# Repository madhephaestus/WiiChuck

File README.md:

# WiiChuck
An Arduino library for talking to every extension controller made for the Wii including the Nunchuk and Classic Controller over I²C.

## Supported Controllers:

* Nunchuk
* Classic Controller
* Guitar Hero Guitar
* Guitar Hero Drums
* DJ Hero
* Drawesome Tablet
* Taiko Drums

# Mapping

All controllers have been mapped across a single readable array so that code written for one Wii accessort can be made generic for all of Wii accessory devices. The values that come from the controller are scaled to a 0-255 range for all analog and for all digital values. Each value is stored in a single byte in the 'values[]' array, a public member of the accessory class.

Initialize the controller first:

```
nunchuck1.begin();
```

In loop, when reading the controller values, first call:

```
nunchuck1.readData();    // Read inputs and update maps
```

Then read the controller values out of the 'values[]' array:

```
uint8_t joystickValueX = nunchuck1.values[1];
uint8_t joystickValueY = nunchuck1.values[2];

...

uint8_t lastValue = nunchuck1.values[19];

```

## Nunchuck mapping

```
values[0]=map(getJoyX(),0,255,0,255);
values[1]=map(getJoyY(),0,255,0,255);
values[2]=map(getRollAngle(),0,1024,0,256);
values[3]=map(getPitchAngle(),0,1024,0,256);
values[4]=map(getAccelX(),0,1024,0,256);
values[5]=map(getAccelY(),0,1024,0,256);

values[6]=map(getAccelZ(),0,1024,0,256);
values[7]=0;
values[8]=0;
values[9]=0;
values[10]=getButtonZ()?255:0;
values[11]=getButtonC()?255:0;
values[12]=0;
values[13]=0;

values[14]=0;
values[15]=0;
values[16]=0;

values[17]=0;
values[18]=0;
```

## Classic Controller Mapping

```
values[0]=map(getJoyXLeft(),0,64,0,256);
values[1]=map(getJoyYLeft(),0,64,0,256);
values[2]=map(getJoyXRight(),0,32,0,256);
values[3]=map(getJoyYRight(),0,32,0,256);
values[4]=0;
values[5]=0;

values[6]=getPadRight()?255:(getPadLeft()?0:128);
values[7]=getPadDown()?0:(getPadUp()?255:128);
values[8]=getButtonX()?255:0;
values[9]=getButtonY()?255:0;
values[10]=getButtonZLeft()?255:0;
values[11]=map(getTriggerLeft(),0,32,0,256);
values[12]=getButtonA()?255:0;
values[13]=getButtonB()?255:0;

values[14]=getButtonMinus()?0:(getButtonPlus()?255:128);
values[15]=getButtonHome()?255:0;
values[16]=0;

values[17]=map(getTriggerRight(),0,32,0,256);
values[18]=getButtonZRight()?255:0;
```

## DJ Table mapping

```
values[0]=map(getCrossfadeSlider(),0,255,0,256);
values[1]=map(getEffectDial(),0,255,0,256);
values[2]=map(getStickX(),0,255,0,256);
values[3]=map(getStickY(),0,255,0,256);
values[4]=map(getRightDJTable(),0,255,0,256);
values[5]=map(getLeftDJTable(),0,255,0,256);

values[6]=getPlusButton()?255:(getMinusButton()?0:128);
values[7]=getEuphoriaButton()?255:0;
values[8]=0;
values[9]=0;
values[10]=getRightBlueButton()?255:0;
values[11]=getRightRedButton()?255:0;
values[12]=getRightGreenButton()?255:0;
values[13]=getLeftBlueButton()?255:0;

values[14]=getLeftRedButton()?255:0;
values[15]=getLeftGreenButton()?255:0;
values[16]=getButtonPlus()?255:0;

values[17]=getButtonZLeft()?255:0;
values[18]=getButtonZRight()?255:0;
```

## Drawesome Mapping

```
values[0] = map(getPenXPosition(), 0, 64, 0, 256);
values[1] = map(getPenYPosition(), 0, 64, 0, 256);
values[2] = map(getPenPressure(), 0, 32, 0, 256);
values[3] = 0;
values[4] = 0;
values[5] = 0;

values[6] = 0;
values[7] = 0;
values[8] = 0;
values[9] = 0;
values[10] = getPenContact() ? 255 : 0;
values[11] = 0;
values[12] = 0;
values[13] = 0;

values[14] = 0;
values[15] = 0;
values[16] = 0;

values[17] = 0;
values[18] = 0;
```

## Drums Mapping

```
values[0]=map(getCrossfadeSlider(),0,255,0,256);
values[1]=map(getEffectDial(),0,255,0,256);
values[2]=map(getStickXGuitar(),0,255,0,256);
values[3]=map(getStickYGuitar(),0,255,0,256);
values[4]=map(getRightDJTable(),0,255,0,256);
values[5]=map(getLeftDJTable(),0,255,0,256);

values[6]=getPlusButtonGuitar()?255:(getMinusButtonGuitar()?0:128);
values[7]=getEuphoriaButton()?255:0;
values[8]=0;
values[9]=0;
values[10]=getRightBlueButton()?255:0;
values[11]=getRightRedButton()?255:0;
values[12]=getRightGreenButton()?255:0;
values[13]=getLeftBlueButton()?255:0;

values[14]=getLeftRedButton()?255:0;
values[15]=getLeftGreenButton()?255:0;
values[16]=getButtonPlus()?255:0;

values[17]=getButtonZLeft()?255:0;
values[18]=getButtonZRight()?255:0;
```

## Guitar Mapping

```
values[0]=map(getWhammyBar(),0,31,0,255);
values[1]=map(getStickXGuitar(),0,63,0,255);
values[2]=map(getStickYGuitar(),0,63,0,255);
values[3]=map(getSlider(),0,31,0,255); // a value of zero means the guitar does not have a slider
values[4]=0;
values[5]=getMinusButtonGuitar()?255:0;
values[6]=getPlusButtonGuitar()?255:0;
values[7]=getStrumUp()?255:(getStrumDown()?0:127);
values[8]=0;
values[9]=getPedalButton()?255:0;
values[10]=getGreenButton()?255:0;
values[11]=getRedButton()?255:0;
values[12]=getYellowButton()?255:0;
values[13]=getBlueButton()?255:0;

values[14]=getOrangeButton()?255:0;
values[15]=0;
values[16]=0;

values[17]=0;
values[18]=0;
```

# Repository Structure
This repository is forked from a curated set of old Arduino Libraries. I kept the old commits and the fork linking to keep attribution to the work done before I picked up the torch. In my mind we all see farther by standing on the shoulders of giants, so it is only proper to give credit where credit is due.

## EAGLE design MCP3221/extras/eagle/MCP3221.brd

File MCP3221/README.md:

# MCP3221 DRIVER

&nbsp;&nbsp;&nbsp;&nbsp;&nbsp;&nbsp;&nbsp;&nbsp;&nbsp;&nbsp;

&nbsp;&nbsp;&nbsp;&nbsp;&nbsp;&nbsp;&nbsp;&nbsp;&nbsp;&nbsp;

&nbsp;&nbsp;&nbsp;&nbsp;&nbsp;&nbsp;&nbsp;&nbsp;&nbsp;&nbsp;

The MCP3221 is a 12-Bit Single-Channel ADC with hardware I2C interface.

This library contains a complete driver for the MCP3221 exposing all its available features. The library also contains configurable functions for obtaining either data or voltage reading from the device, as well as applying smoothing methods (Rolling-Average / Exponential-Moving-Average) to the said data/voltage readings. In addition, the library offers a built-in mechanism for calculating input from either 5V or 12V sources (the latter requiring a hardware voltage divider as the AIN pin of the MCP3221 cannot take more than 5.5V).

[MCP3221 DATASHEET](http://ww1.microchip.com/downloads/en/DeviceDoc/21732D.pdf)

## Repository Contents

- **MCP3221.h** - Library Header file.  
- **MCP3221.cpp** - Library Compilation file.  
- **/utility**   
  - **MCP3221InfoStr.h** - Header file containing a functional extention of the library to include generating printable information String (see Note #2 below).  
  - **MCP3221ComStr.h** - Header file containing a functional extention of the library to include generating a printable I2C Communication Result String (see Note #3 below).  
  - **MCP3221_PString.h** - Header file for PString class (lighter alternative to String class).  
  - **MCP3221_PString.cpp** - Compilation file for PString class (lighter alternative to String class).  
- **/examples**   
  - **/MCP3221_Test**  
    - **MCP3221_Test.ino** - A basic sketch for testing whether the MCP3221 is hooked-up and operating correctly.  
  - **/MCP3221_Usage**  
    - **MCP3221_Usage.ino** - A much more extensive sketch offering a complete usage illustration, as well as a rubust testing mechanism.  
  - **/MCP3221_Info**  
    - **MCP3221_Info.ino** - A short sketch showing how to generate a Printable Device Information String with the MCP3221's current settings.  
  - **/MCP3221_I2C_Status**
    - **MCP3221_I2C_Status.ino** - A short sketch for verifying I2C communication has been established between the controller (master) and the MCP3221 (slave).  
- **/extras**
  - **License.txt** - A cope of the end-user license agreement.  
  - **/eagle**
    - **MCP3221.sch** - Schematic file for the MCP3221 breakout board.
    - **MCP3221.brd** - Board layout for the MCP3221 breakout board.
- **keywords.txt** - Keywords for this library which will be highlighted in sketches within the Arduino IDE. 
- **library.properties** - General library properties for the Arduino's IDE (>1.5) Library Package Manager.
- **README.md** - The readme file for this library.
- **library.json** - JSON file for the Arduino's IDE (>1.5) Package Manager.

## HOOK-UP
* __PIN 1 (VCC/VREF)__ - Serves asimultaniously as Power Supply input and Voltage Reference for the ADC. Connect 5V output of Arduino's' or other equivalent power source (5.5V max). However, if using external power source, remember to connect all GND's together.
* __PIN 2 (GND)__ - Connect to Arduino GND
* __PIN 3 (VIN)__ - Connect input voltage to be measured (RANGE: GND - VCC, Min: 0V, Max: 5.5V). For higher voltage readings (e.g. Min: 8.444V, Max: 12.881V), use a voltage divider (Resistor 1: 10K; Resisor 2: 4K7)
* __PIN 4 (SDA)__ - Connect to Arduino's PIN A4 with a 2K2 (400MHz I2C Bus speed) or 10K (100MHz I2C Bus speed) pull-up resistor
* __PIN 5 (SCL)__ - Connect to Arduino's PIN A5 with a 2K2 (400MHz I2C Bus speed) or 10K (100MHz I2C Bus speed) pull-up resistor
* __DECOUPING__: Minimal decoupling consists of a 0.1uF Ceramic Capacitor between the VCC & GND PINS. For improved performance, add a 1uF and a 10uF Ceramic Capacitors as well across these pins.

## GENERAL NOTES

1) __I2C Communications Library Dependency__

This library depends on the Arduino IDE's native [Wire](https://github.com/arduino/Arduino/tree/master/hardware/arduino/avr/libraries/Wire) library for I2C communication between the Arduino (Master) and the MCP3221 (Slave). 

2) __Device Information String__

It possible to extend the MCP3221 Library to include a function for generating a pritable device information string showing all the relevant details about the devices current Configuration, Limit & Hysteresis settings. As the additional functionality comes at the cost of increased memory footprint, it was implemented as an optional add-on rather than added directly to the core MCP3221 Library. See the [MCP3221_Info](https://github.com/nadavmatalon/MCP3221/blob/master/examples/MCP3221_Info/MCP3221_Info.ino) example sketch for detailed explanation and an actual usage demo.

3) __Device I2C Communications String__

It is also possible to extend the MCP3221 Library to include a function for generating a pritable I2C Communications string showing the result of each I2C transaction in a human-friendly way, something that may be useful, for example, during debugging sessions. As the additional functionality comes at the cost of increased memory footprint, it was implemented as an optional add-on rather than added directly to the core MCP3221 Library. See the [MCP3221_I2C_Status](https://github.com/nadavmatalon/MCP3221/blob/master/examples/MCP3221_I2C_Status/MCP3221_I2C_Status.ino) example sketch for detailed explanation and an actual usage demo.

## I2C ADDRESSES

Each MCP3221 has 1 of 8 possible I2C addresses (factory hardwired & recognized by its specific part number & top marking on the package itself):

|PART NO.         | BIN      | HEX  | DEC | MARKING |
|-----------------|----------|------|-----|---------|
| MCP3221A0T-E/OT | 01001000 | 0x48 | 72  | GE      |
| MCP3221A1T-E/OT | 01001001 | 0x49 | 73  | GH      |
| MCP3221A2T-E/OT | 01001010 | 0x4A | 74  | GB      |
| MCP3221A3T-E/OT | 01001000 | 0x4B | 75  | GC      |
| MCP3221A4T-E/OT | 01001100 | 0x4C | 76  | GD      |
| MCP3221A5T-E/OT | 01001101 | 0x4D | 77  | GA      |
| MCP3221A6T-E/OT | 01001110 | 0x4E | 78  | GF      |
| MCP3221A7T-E/OT | 01001111 | 0x4F | 79  | GG      |

## LIBRARY INSTALLATION & SETUP

Begin by installing the library either by using the Arduino IDE's Installation Wizard (Arduino Version >1.5) or simply download the library's ZIP folder from GITHUB, extract it, and copy the extraxcted folder to your Arduino 'libraries' folder.

Next, include the library at the top of the sketch as follows:

```
#include "MCP3221.h"
```

At this point you can construct a new MPC3221 instance(s) by using the following command (at the top of the sketch after the 'include' line):

```
MPC3221 device_name(device_address);
```

>Replace '__device_name__' with a name of your choice. Also, remember to replace  '__device_address__' with the specific I2C address of your device (see I2C ADDRESSES Section above).

Next, make sure to include an instruction for initializing the I2C Bus for the [Wire](https://github.com/arduino/Arduino/tree/master/hardware/arduino/avr/libraries/Wire) Library, as follows:

>There's no need to include the [Wire](https://github.com/arduino/Arduino/tree/master/hardware/arduino/avr/libraries/Wire) Library at the top of the sketch as it's already included internally by the MCP3221 Library

```
void setup() {
    Wire.begin();
    // ...other setup code...
}
```

## LIBRARY FUNCTIONS

With the library installed & included in the sketch, and an MCP3221 instance created, the following functions are available (see the usage example sketch for a detailed implementation):

__Note About Methods' Return Values:__  
All 'get' methods return some sort of value (e.g. temp reading, hysteresis setting, etc.), while all 'set' methods return nothing. Nevertheless, ALL methods implicitly update the library's __I2C _comBuffer__ (=communication buffer) after each I2C transmission. The reason for this functional design is to maintain structural coherance between the 'get' and 'set' methods. As 'get' methods cannot return both the desired value and the I2C transmission's result simultaniously. Consequently, if the relevant value hasn't been obtained by a particular 'get' method, the user can simply check the content of the _comBuffer to see what error occured. Similarly, it is possible to check if a particular setting has been successfully applied via a 'set' method either by preforming the corresponding 'get' method - e.g. getHystC() after using setHystC() - or by checking the content of the _comBuffer (0 indicates a successful transmission, 1-6 indicate an error as listed below). 

__ping();__                                    
Parameters:&nbsp;&nbsp;&nbsp;None  
Description:&nbsp;&nbsp;&nbsp;Searches for the MCP3221 at the pre-defined I2C Bus address &amp; returns byte with the relevant success/error code, as follows:  
0  ...  Success (no error)  
1  ...  Buffer overflow  
2  ...  Address sent, NACK received  
3  ...  Data send, NACK received  
4  ...  Other error (lost bus arbitration, bus error, etc.)  
5  ...  Timed-out while trying to become Bus Master  
6  ...  Timed-out while waiting for data to be sent  
\>6 ... Unlisted error (potential future implementation/s)<br>
Returns:&nbsp;&nbsp;&nbsp;&nbsp;&nbsp;&nbsp;&nbsp;&nbsp;&nbsp;byte  

__getVref();__  
Parameters:&nbsp;&nbsp;&nbsp;None  
Description:&nbsp;&nbsp;&nbsp;Gets the current setting of the 'Voltage Reference' parameter in mV (default: 4096mV). Acceptable range: 2700-5500mV.   
Returns:&nbsp;&nbsp;&nbsp;&nbsp;&nbsp;&nbsp;&nbsp;&nbsp;unsigned int  

__getRes1();__  
Parameters:&nbsp;&nbsp;&nbsp;None  
Description:&nbsp;&nbsp;&nbsp;Gets the current value of Resistor 1 (in Ω) of the hardware voltage divider (if used). Set automatically to 0Ω if device is initialized with Voltage Input set to 5V (default), or to 10KΩ if device is initialized with Voltage Input set to 12V (value can be changed after device initialization).  
Returns:&nbsp;&nbsp;&nbsp;&nbsp;&nbsp;&nbsp;&nbsp;&nbsp;unsigned int  

__getRes2();__  
Parameters:&nbsp;&nbsp;&nbsp;None  
Description:&nbsp;&nbsp;&nbsp;Gets the current value of Resistor 2 (in Ω) of the hardware voltage divider (if used). Set automatically to 0Ω if device is initialized with Voltage Input set to 5V (default), or to 4K7Ω if device is initialized with Voltage Input set to 12V (value can be changed after device initialization).  
Returns:&nbsp;&nbsp;&nbsp;&nbsp;&nbsp;&nbsp;&nbsp;&nbsp;unsigned int  

__getAlpha();__  
Parameters:&nbsp;&nbsp;&nbsp;None  
Description:&nbsp;&nbsp;&nbsp;Gets the current value of the 'Alpha' parameter used by the 'EMAVG' smoothing method (default: 178).  
Returns:&nbsp;&nbsp;&nbsp;&nbsp;&nbsp;&nbsp;&nbsp;&nbsp;unsigned int  

__getNumSamples();__  
Parameters:&nbsp;&nbsp;&nbsp;None  
Description:&nbsp;&nbsp;&nbsp;Gets the current number of samples used by the 'Rolling-Average' smoothing method (default: 10 Samples).  
Returns:&nbsp;&nbsp;&nbsp;&nbsp;&nbsp;&nbsp;&nbsp;&nbsp;byte  

__getVinput();__  
Parameters:&nbsp;&nbsp;&nbsp;None  
Description:&nbsp;&nbsp;&nbsp;Gets the voltage input settings (5V [default] / 12V) used for voltage reading calculations.  
Returns:&nbsp;&nbsp;&nbsp;&nbsp;&nbsp;&nbsp;&nbsp;&nbsp;byte   

__getSmoothing();__  
Parameters:&nbsp;&nbsp;&nbsp;None  
Description:&nbsp;&nbsp;&nbsp;Gets the current smoothing method (0 = NO SMOOTHING / 1 = ROLLING-AVERAGE / 2 = EMAVG [default]) used for voltage reading calculations.  
Returns:&nbsp;&nbsp;&nbsp;&nbsp;&nbsp;&nbsp;&nbsp;&nbsp;byte   

__getData();__  
Parameters:&nbsp;&nbsp;&nbsp;None  
Description:&nbsp;&nbsp;&nbsp;Gets the latest conversion data from the device (the data is automatically smoothed by the selected smoothing method if used). To obtain raw data from the device simply set the Smoothing Method settings to 'NO SMOOTHING'.  
Returns:&nbsp;&nbsp;&nbsp;&nbsp;&nbsp;&nbsp;&nbsp;&nbsp;unsigned int  

__getVoltage();__  
Parameters:&nbsp;&nbsp;&nbsp;None  
Description:&nbsp;&nbsp;&nbsp;Gets the latest voltage reading (in mV) from the device (the reading is automatically smoothed by the selected smoothing method if used). To obtain unmodified voltage readings from the device simply set the Smoothing Method settings to 'NO SMOOTHING'.   
Returns:&nbsp;&nbsp;&nbsp;&nbsp;&nbsp;&nbsp;&nbsp;&nbsp;unsigned int  

__getComResult();__  
Parameters:&nbsp;&nbsp;&nbsp;None  
Description:&nbsp;&nbsp;Returns the latest I2C Communication result code (see Success/Error codes above)  
Returns:&nbsp;&nbsp;&nbsp;&nbsp;&nbsp;&nbsp;&nbsp;&nbsp;byte  

__setVref();__  
Parameters:&nbsp;&nbsp;&nbsp;unsigned int  
Description:&nbsp;&nbsp;&nbsp;Sets the current value of the 'Voltage Reference' parameter (in mV). This value can be obtained by measuring the input voltage on the devices VCC pin    
Returns:&nbsp;&nbsp;&nbsp;&nbsp;&nbsp;&nbsp;&nbsp;&nbsp;None  

__setRes1();__  
Parameters:&nbsp;&nbsp;&nbsp;unsigned int  
Description:&nbsp;&nbsp;&nbsp;sets the current value of Resistor 1 (in Ω) of the hardware voltage divider (if used)  
Returns:&nbsp;&nbsp;&nbsp;&nbsp;&nbsp;&nbsp;&nbsp;&nbsp;None  

__setRes2();__  
Parameters:&nbsp;&nbsp;&nbsp;unsigned int  
Description:&nbsp;&nbsp;&nbsp;Sets the current value of Resistor 2 (in Ω) of the hardware voltage divider (if used)  
Returns:&nbsp;&nbsp;&nbsp;&nbsp;&nbsp;&nbsp;&nbsp;&nbsp;None  

__setAlpha();__  
Parameters:&nbsp;&nbsp;&nbsp;unsigned int  
Description:&nbsp;&nbsp;&nbsp;Sets the current value of the 'Alpha' parameter (used by the 'EMAVG' smoothing method). Acceptable range: 0-256 (attempting to set this parameter to lower/heigher values, sets actual value to minimum/maximum respectively).   
Returns:&nbsp;&nbsp;&nbsp;&nbsp;&nbsp;&nbsp;&nbsp;&nbsp;None  

__setNumSamples();__  
Parameters:&nbsp;&nbsp;&nbsp;byte  
Description:&nbsp;&nbsp;&nbsp;Sets the current number of samples used by the 'Rolling-Average' smoothing method. Acceptable range: 1-20 samples (attempting to set this parameter to lower/heigher values, sets actual value to minimum/maximum respectively).   
Returns:&nbsp;&nbsp;&nbsp;&nbsp;&nbsp;&nbsp;&nbsp;&nbsp;byte  

__setVinput();__  
Parameters:&nbsp;&nbsp;&nbsp;VOLTAGE_INPUT_5V [default] / VOLTAGE_INPUT_12V  
Description:&nbsp;&nbsp;&nbsp;Sets the voltage input parameter (5V or 12V) which is used for voltage reading calculations  
Returns:&nbsp;&nbsp;&nbsp;&nbsp;&nbsp;&nbsp;&nbsp;&nbsp;None   

__setSmoothing();__  
Parameters:&nbsp;&nbsp;&nbsp;NO_SMOOTHING / ROLLING_AVERAGE / EMAVG  
Description:&nbsp;&nbsp;&nbsp;Sets the current smoothing method used for voltage reading calculations  
Returns:&nbsp;&nbsp;&nbsp;&nbsp;&nbsp;&nbsp;&nbsp;&nbsp;None     

__reset();__  
Parameters:&nbsp;&nbsp;&nbsp;None  
Description:&nbsp;&nbsp;&nbsp;Resets the device to its default settings  
Returns:&nbsp;&nbsp;&nbsp;&nbsp;&nbsp;&nbsp;&nbsp;&nbsp;None  

__Destructor__  
If you want to destruct an instantiated MCP3221 object, you can use the following method to do so:  

```
~MCP3221 device_name();
```
>Replace '__device_name__' with the name of your MCP3221 instance.

## Extended Functionality*

(* requires an additional '\#include' of the relevant *.h file as shown in the corresponding example sketches)  

__MCP3221ComStr();__  
Parameters:&nbsp;&nbsp;&nbsp;Name of an initialized MCP3221 instance  
Description:&nbsp;&nbsp;Returns printable string containing human-friendly information about the device's latest I2C communication result  
Returns:&nbsp;&nbsp;&nbsp;&nbsp;&nbsp;&nbsp;&nbsp;&nbsp;PString  

__MCP3221InfoStr();__  
Parameters:&nbsp;&nbsp;&nbsp;Name of an initialized MCP3221 instance  
Description:&nbsp;&nbsp;Returns printable string containing detailed information about the device's current settings  
Returns:&nbsp;&nbsp;&nbsp;&nbsp;&nbsp;&nbsp;&nbsp;&nbsp;PString  

## RUNNING THE EXAMPLE SKETCH

1) Start the Arduino IDE and open the relevant example sketch  
1) Hook-up the MCP3221 to the Arduino as explained in the sketch's notes   
2) Upload the sketch to the Arduino  
3) Open the Serial Communications Window (make sure the baud-rate is set to 9600 or change it in the sketch to match your Serial Port's buad-rate)  

## BUG REPORTS

Please report any issues/bugs/suggestions at the [Issues](https://github.com/nadavmatalon/MCP3221/issues) section of this Github repository.

## TODO

## VERSION HISTORY

__Ver. 1.0.0__ - First release (16.10.16)  

## LICENSE

[The MIT License (MIT)](https://opensource.org/licenses/MIT)
Copyright (c) 2016 Nadav Matalon

Permission is hereby granted, free of charge, to any person obtaining a copy of this software and associated documentation files (the "Software"), to deal in the Software without restriction, including without limitation the rights to use, copy, modify, merge, publish, distribute, sublicense, and/or sell copies of the Software, and to permit persons to whom the Software is furnished to do so, subject to the following conditions:

The above copyright notice and this permission notice shall be included in all copies or substantial portions of the Software.

THE SOFTWARE IS PROVIDED "AS IS", WITHOUT WARRANTY OF ANY KIND, EXPRESS OR IMPLIED, INCLUDING BUT NOT LIMITED TO THE WARRANTIES OF MERCHANTABILITY, FITNESS FOR A PARTICULAR PURPOSE AND NONINFRINGEMENT. IN NO EVENT SHALL THE AUTHORS OR COPYRIGHT HOLDERS BE LIABLE FOR ANY CLAIM, DAMAGES OR OTHER LIABILITY, WHETHER IN AN ACTION OF CONTRACT, TORT OR OTHERWISE, ARISING FROM, OUT OF OR IN CONNECTION WITH THE SOFTWARE OR THE USE OR OTHER DEALINGS IN THE SOFTWARE.

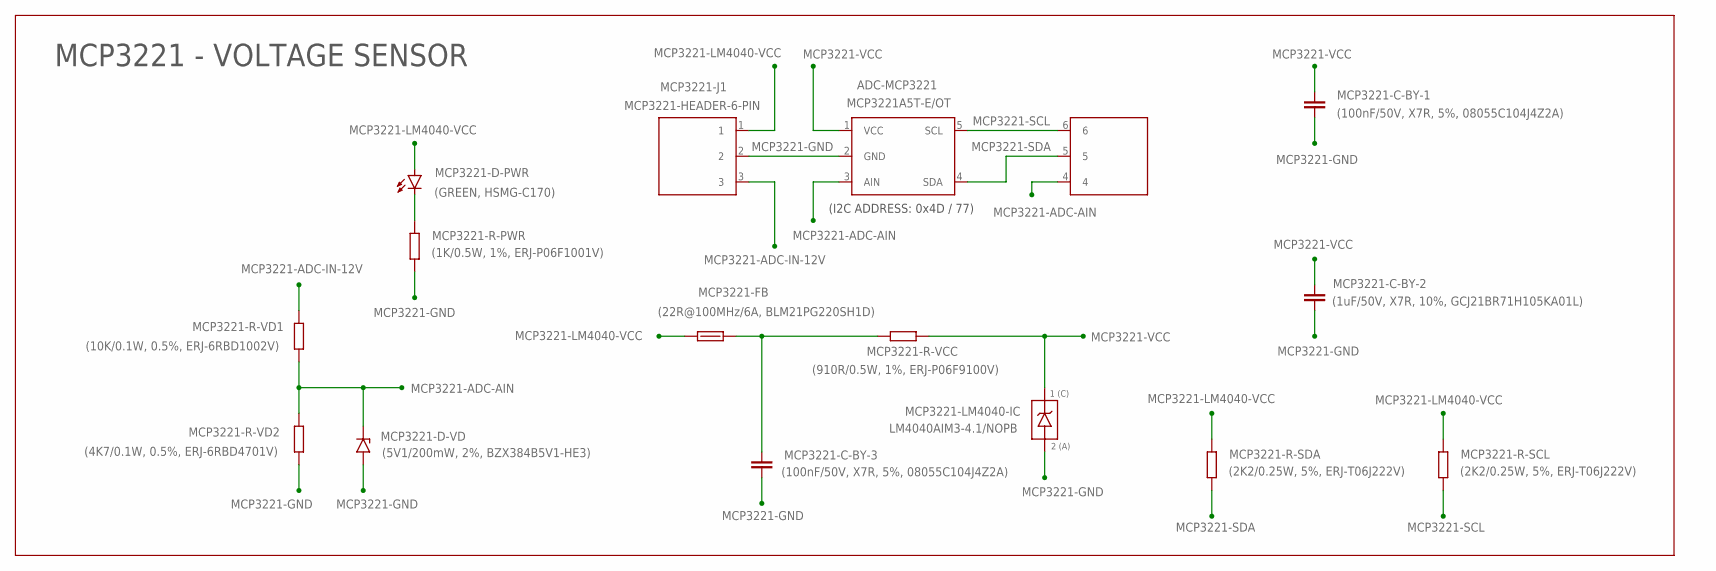
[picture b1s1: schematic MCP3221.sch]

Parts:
ADC-MCP3221: MCP3221A5T-E/OT; SOT-23-5
MCP3221-C-BY-1, MCP3221-C-BY-3: (100nF/50V, X7R, 5%, 08055C104J4Z2A); 0805
MCP3221-C-BY-2: (1uF/50V, X7R, 10%, GCJ21BR71H105KA01L); 0805
MCP3221-D-PWR: (GREEN, HSMG-C170); DIODE_0805
MCP3221-D-VD: (5V1/200mW, 2%, BZX384B5V1-HE3); SOD-323-DIODE
MCP3221-FB: (22R@100MHz/6A, BLM21PG220SH1D); 0805
MCP3221-J1: MCP3221-HEADER-6-PIN; HEADER_2.54MM_6_PIN_VER
MCP3221-LM4040-IC: LM4040AIM3-4.1/NOPB; SOT-23-3
MCP3221-R-PWR: (1K/0.5W, 1%, ERJ-P06F1001V); 0805
MCP3221-R-SCL, MCP3221-R-SDA: (2K2/0.25W, 5%, ERJ-T06J222V); 0805
MCP3221-R-VCC: (910R/0.5W, 1%, ERJ-P06F9100V); 0805
MCP3221-R-VD1: (10K/0.1W, 0.5%, ERJ-6RBD1002V); 0805
MCP3221-R-VD2: (4K7/0.1W, 0.5%, ERJ-6RBD4701V); 0805

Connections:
MCP3221-ADC-AIN: ADC-MCP3221.3 (AIN), MCP3221-D-VD.C, MCP3221-J1.4, MCP3221-R-VD1.2, MCP3221-R-VD2.1
MCP3221-ADC-IN-12V: MCP3221-J1.3, MCP3221-R-VD1.1
MCP3221-GND: ADC-MCP3221.2 (GND), MCP3221-C-BY-1.2 (C), MCP3221-C-BY-2.1 (A), MCP3221-C-BY-3.2 (C), MCP3221-D-VD.A, MCP3221-J1.2, MCP3221-LM4040-IC.2 (A), MCP3221-LM4040-IC.3 (A), MCP3221-R-PWR.1, MCP3221-R-VD2.2
MCP3221-LM4040-VCC: MCP3221-D-PWR.A, MCP3221-FB.2, MCP3221-J1.1, MCP3221-R-SCL.2, MCP3221-R-SDA.2
MCP3221-LM4040_VCC_FILTERED: MCP3221-C-BY-3.1 (A), MCP3221-FB.1, MCP3221-R-VCC.2
MCP3221-PWR: MCP3221-D-PWR.C, MCP3221-R-PWR.2
MCP3221-SCL: ADC-MCP3221.5 (SCL), MCP3221-J1.6, MCP3221-R-SCL.1
MCP3221-SDA: ADC-MCP3221.4 (SDA), MCP3221-J1.5, MCP3221-R-SDA.1
MCP3221-VCC: ADC-MCP3221.1 (VCC), MCP3221-C-BY-1.1 (A), MCP3221-C-BY-2.2 (C), MCP3221-LM4040-IC.1 (C), MCP3221-R-VCC.1

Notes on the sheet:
(I2C ADDRESS: 0x4D / 77)
MCP3221 - VOLTAGE SENSOR

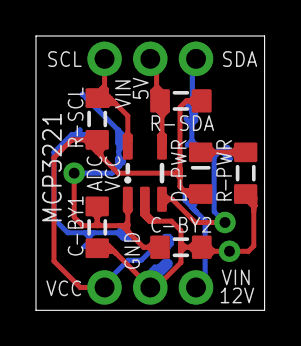
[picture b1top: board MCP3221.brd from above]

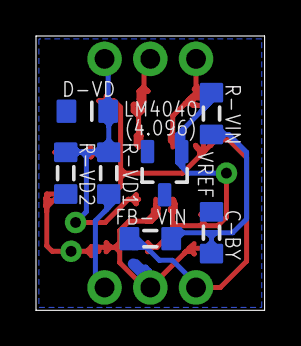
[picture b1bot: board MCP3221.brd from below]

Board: 2 copper layers, 12.7 x 15.2 mm, 15 parts (7 on the bottom side), 9 nets.

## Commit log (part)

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2017-01-07 :space_invader: Added .gitattributes
2017-01-07 2017.01.07
2017-01-12 2017.01.12
2017-01-14 2017.01.14
2017-01-17 2017.01.18
2017-01-20 2017.01.20
2017-01-26 Removing all other libraries except WiiChuck
2017-01-26 Moving all files up to the top directory
2017-01-26 ignore
2017-01-26 Adding a generic hardware profile
    this profile defaults to software IO.
2017-01-29 Using local shift out function
2017-01-29 adding a spacing to the shift out function
2017-01-29 more robust bit masking
2017-01-29 Initialization standardized
    All conttollers call back to an initialization function, which selects
    the initialization bytes based on controller type. Official controllers
    are supported under one mode, and third party ones under another.
    Control bytes are sent each frame to ensure disconnects are dealt with.
2017-01-29 C and Z buttons mapped
    The C and Z button bits are now read correctly.
2017-01-30 Adding Wiiclassic interface
    Functions from :
    https://github.com/JorjBauer/swd40/blob/18641e44cdc73d73278f9fce3977b19f526c20fe/arduino_wii_controller/wii-dev-code/WiiClassic.h
2017-01-30 Adding the function calls for controller classic
    the controller classic functions are just alternate way to read the data
    synced in normal operation. THese functions return valid data when a
    controller classic is connected, and indeterminate data when an nunchuck
    is connected.
2017-01-30 basic map tree
2017-01-30 preparing for release.
2017-01-30 adding comments to the map
2017-01-30 more comments
2017-01-30 0.0.2
2017-02-04 Dynamic bounding of upper and lower bound
2017-02-05 adding a stall checking function
2017-02-05 implementing stall check
2017-02-05 wrap the clock pin transition in clock check
2017-02-05 tighter ack timeout
2017-02-05 removing the stack overflow
    a copy paste error caused an infinite recoursion
2017-02-06 minimizing access to pin mode
2017-02-06 0.0.4
    The data randomizing math is removed.
    This seems to be a way to deal with the buttons, but applied in the
    wrong place.
2017-02-06 Stripping the hardware layer
    Using Wire to deal with any hardware i2c functions
2017-02-06 Allow user to select pullup mode
    Users can use pullup mode. Default is driven clock mode.
2017-02-06 Defaulting to no pullups
    Default configuration is no pullups
2017-02-06 initialize wire
2017-02-06 use pull ups for both data and clock
    In I2c both the data and clock are weak pull high, drive low
    configurations.
2017-02-06 0.0.6
2017-02-06 fixing the IO mapping
2017-02-07 defaulting the example to forced clock mode
2017-02-07 rev bump 0.0.7
2017-02-11 classic controller startup
2017-02-11 read 8 bytes for wii classic
2017-02-11 remove junk wait in waitForAck
2017-02-11 0.0.9
2017-02-11 Fixed init code
2017-02-12 0.0.10
2017-02-12 removing the unneeded headers
2017-02-12 removing junk demo
2017-02-12 0.0.11
2017-02-12 0.0.12
2017-02-12 Added delay after init. Makes classic controller work.
2017-02-12 Only Init's once.
2017-02-12 Controller Identification Function
2017-02-12 Alexs changes to allow for classic controller
2017-02-12 0.0.14
2017-02-12 0.0.15 Moving to Enum based controller type
    The controller type is read off from the device and stored in the
    WiiChuck object.
2017-02-12 adding keywords of the types of controllers
2017-02-12 example tweaks
2017-02-12 moved files into src and began working on accessory class
2017-02-12 int dissection code working
2017-02-12 use classic controller
2017-02-12 removing old cpp files
2017-02-12 no CSG database
2017-02-12 remove junk
2017-02-12 Adding coms layer to the accery class
2017-02-12 mapping struct
2017-02-12 began cleanup
2017-02-12 More cleanup
2017-02-12 compile error fixes
2017-02-12 Cleared out old vars that where preventing compile
2017-02-12 fixed odd capitalization
2017-02-12 removed old constructors
2017-02-12 connects to device
2017-02-12 made tings that should be private private and cleaned up class def
2017-02-12 setter for pullup clock
2017-02-13 sorting functions
2017-02-13 removing dead code
2017-02-13 funcs for input mappint
2017-02-13 #defined labels for bits and bytes to make controller definitions easier to read
2017-02-13 fixed enum and detection
2017-02-13 Generic accesory demo ino
2017-02-13 renamed
2017-02-13 Fixing imports
2017-02-13 cleanup
2017-02-13 adding api
2017-02-13 fixes compilation
2017-02-13 moving the data array to protected
2017-02-13 adding correct subclass constructors
2017-02-13 cleaned the print
2017-02-13 adding function headers
2017-02-13 Adding the default methods for function map
2017-02-13 Afdding the implementation
2017-02-13 Added bits for joy X
2017-02-13 Added bits for accel X
2017-02-13 adding the double mapping
2017-02-13 Added Button C
2017-02-13 adding the mappings
2017-02-13 compile errors
2017-02-13 Adding scaling
2017-02-13 fixed compilation
2017-02-13 Fixed mapping function and fixed scaling info in map struct
2017-02-13 changed print func to display accelerations and removed offsets.
2017-02-13 removed enum with button types
2017-02-13 Mapping linked list
2017-02-13 Digital and Analog add map funcs done. Printing of active maps done.
2017-02-13 Removed old mapping code
2017-02-13 Servo mapping works
2017-02-13 sample sketch for raw mapping
2017-02-14 pulled out sw i2c into its own class
2017-02-14 iic was broken all along O_O . Removed switch so it uses Wire now
2017-02-15 New mapping function using c++ objects
2017-02-16 Encrypted mode
2017-02-17 classic controller
2017-02-21 Cleaned up drawesome code
2017-02-22 Tablet works in unenc mode
2017-02-22 Guitar works
2017-02-23 Added support for drums
2017-02-23 Changed around some of the arguments and returns of various functions. Added a "cooldown" timer" for inputs
2017-02-23 Added cooldown to most mapping classes
2017-02-23 removed debug prints
2017-02-23 Removed old examples and added an example for drums
2017-03-14 Updating mapping for unimplemented Classic Controller buttons
2017-03-14 Reducing length of string sent to serial
    Due to the number of buttons on the classic controller, the serial debug
    output can get exceptionally long.
    I'm not attached to this change, so feel free to reject it without any
    hard feelings. It just made things easier for my debugging.
2017-03-20 adding additional examples
2017-03-20 controller mapping working
2017-05-20 Fixed input values jumping out of range
2017-08-02 Example to demonstrate #3
2017-08-02 Adding Classic Controller example
2017-09-02 Use correct separator in keywords.txt (#5)
    The Arduino IDE requires the use of a tab separator between the name and identifier. Without this tab the keyword is not highlighted.
    Reference: https://github.com/arduino/Arduino/wiki/Arduino-IDE-1.5:-Library-specification#keywords
2017-10-16 Create LICENSE (#7)
    Close #6
2017-10-16 Justify commit history
    Addresses #8
2017-10-17 Get bytes read in readData
2017-10-17 Switch burstRead to boolean
2017-10-17 Switch readData to boolean
2017-10-17 Restrict new maps to successful read
    Prevents junk data from being mapped
2017-10-17 Serial Default on Print Statements (#12)
    * Added serial defaults to prints
    * Removed serial keyword from examples
2017-11-07 Removed duplicate assignment (#15)
    Whoops!
2017-11-07 Nunchuk Pitch + Roll Angle Updates (#14)
    * Changed output to float
    No reason to do floating point calculations and return an int
    * Get roll full range
    (1023 max - 1 min) / 2 = 511
    * Get pitch full range
    (1023 max - 1 min) / 2 = 511
2017-11-07 Multiplexer Functions (#13)
    * Add multiplexer functions
    * Call multiplexer switches
    * Add multiplexer keyword
    * Add static multiplex function
    Useful if you only need to set the multiplexer once, e.g. running only
    one controller on a multi-capable board
2017-11-08 Reduce I2C buffer size (#9)
    * Reduce I2C buffer size (faster bus comms)
    * Removed setData define
    * Changed dataArray size
2017-11-08 Removed default multiplexer address
2017-11-08 Separated multiplexer helper function
2017-11-08 Set multiplex helper to private
    C'mon git, work with me here...
2017-11-08 Start I2C in static multiplexer function
    Required if `switchMultiplexer` is called before `begin`
2017-11-08 Removed Software I2C References (#18)
    * Remove sWire
    * Remove SDA/SCL constructors
    * Removed 'myWire'
2017-11-09 Housecleaning (#19)
    * Removed unused I2C defines
    * Added wire check to begin function
    Don't restart the bus if it's already active
    * Removed old type macros
    * Cleaned accessory header whitespace
    * Move classic controller below nunchuck
2017-11-09 Reduced delay in readData (#20)
2017-11-09 Version bump
2017-11-09 Reworked all whitespace (#21)
    Consistent indentation (tabs rather than mixed), proper indentation, and
    reduced # of extra lines
2017-11-12 Reworked Examples (#22)
    * Removed 'Arduino' folder
    It's an Arduino library, after-all
    * Controller-specific example folders
    * Renamed examples
    "_Example" is implicit
    * Reworked example whitespace
2017-11-12 Changed button functions to use 'get' prefix
    Matches every other user-facing function in the library
2017-11-12 Removed brackets from switch case
    Improper syntax
2017-11-12 Keyword Updates (#24)
    * Add section labels to keywords
    * Removed old SI2C defines
    * Added switchMultiplexer function
    * Added controller type keywords
    * Updated checkButton to getButton
    * Added all controller functions
2018-02-09 Compatible with esp32 (#27)
2018-02-10 Revert "Compatible with esp32 (#27)"
    This reverts commit e054609d5a52a4122f526901b97b39c26256382c.
2018-02-12 Changing the defuult defines
2018-03-06 Adding wire failure retry (#31)
    * Updating to 0.0.24
    * Adding a failure check on the transaction end transmission
2018-03-18 Adding non-esp32 compile back in (#33)
    * Updating to 0.0.24
    * Adding a failure check on the transaction end transmission
    * Adding retry to all i2c transmissions
    * clarifying the failover retry
    * Compile for non esp32 working
    * Compile for non esp32 working
2018-03-18 0.0.26
2018-04-08 Simplified API for Wii devices (#34)
    * Updating to 0.0.24
    * Adding a failure check on the transaction end transmission
    * Adding retry to all i2c transmissions
    * clarifying the failover retry
    * Compile for non esp32 working
    * Compile for non esp32 working
2018-04-15 Updating master to the new API (#35)
    * Updating to 0.0.24
    * Adding a failure check on the transaction end transmission
    * Adding retry to all i2c transmissions
    * clarifying the failover retry
    * Compile for non esp32 working
    * Compile for non esp32 working
2018-04-17 spelling
2018-04-21 Adding esp32 servo header
2018-04-21 0.1.2
2018-04-21 Release 0.1.2 (#36)
    * spelling
    * Adding esp32 servo header
    * 0.1.2
2018-05-01 Updaing the servo map
2018-06-16 updaing the wii lib
2018-06-16 Adding the new version
2018-06-16 Adding a check for ESP and slow down the I2C
2018-06-28 Stabalize the reads and reject bad packets
2018-06-28 Make each read match the previous before allowed to pass
2018-07-29 CLeanly detecting bad packets and not getting stuck
2018-07-30 better filtering of bad data
2018-08-10 COmpiling check
2018-09-13 Improving the fail over stability
2018-10-20 Removing prints that cause fault
2019-03-03 Removing the spurrious retry stack
2019-03-04 Changing controller mapping
2023-05-10 Add support for the pedal port on some Wii guitars
2023-05-10 Bump version
2023-05-10 Add support for the neck slider on GH:WT and later guitars
2023-05-10 Fix whammy bar mapping range
2023-05-10 Add X and Y stick values to the guitar values array
2023-05-10 Split plus and minus buttons into separate values instead of an axis
2023-05-10 Bump version to 0.3.4
2023-05-16 Return guitar slider reading only if one is present
2023-05-16 Sync values arrays between code and README for all peripherals
2023-05-16 Remove DJ table and redundant values from guitar mappings
